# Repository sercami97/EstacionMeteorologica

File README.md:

# Estacion Meteorológica Inteligente de Bajo Costo

El objetivo del proyecto es diseñar una estación meteorológica inteligente. Esto es, que sea capaz de usar protocolos de IoT para el almacenamiento de los datos en un servidor remoto y ser autosostenible (Energía solar). Además, se espera que los diseños sean fácilmente replicables y tengan un bajo costo. Esto con el objetivo de ser más acesible para las comunidades campesinas y lograr un mayor impacto.

## Comenzando
Descarga o clona el repositorio a tu maquina local. En la capeta ../CodigoArduino/DATA_SERVIDOR_NSM encontrarán el codigo fuente del proyecto (Arduino). Por otro lado, en la carpeta ../PCB/LATEST/PCB_final se encuentran los archivos pertinentes al diseño de la PCB del proyecto. Dentro de esta misma carpeta, en ../GerberSleep se encuentran los archivos gerber listos para mandar a producción. Finalmente, en ../Diseños3D se encuentran los archivos de los diseños 3D desarrollados para la estructura de la estación. 

### Pre-requisitos
Es necesario tener instalados los siguientes sowftware para acceder a los archivos del proyecto:
- Arduino
- KiCad EDA
- Autodesk Inventor
- Libería de Arduino "DHT.h" https://github.com/adafruit/DHT-sensor-library/archive/master.zip
- Libería de Arduino "Arduino.h"
- Libería de Arduino "Wire.h"
- Libería de "ArduinoSoftwareSerial.h"
- Libería de Arduino "DS3232RTC.h" https://github.com/JChristensen/DS3232RTC

### Instalación
Para contar con un prototipo del proyecto debes:
- Imprimir, soldar y armar PCB (En la wiki se describe con mejor detalle como hacer esto junto con los componentes necesarios).
- Imprimir y replicar piezas 3D (En la wiki se describe con mejor detalle como hacer esto junto con los materiales necesarios).
- Armar estación (En la wiki se describe con mejor detalle como hacer esto junto con las piezas necesarias).

### Ejecutando pruebas

#### 1. Codigo Arduino
Para probar la funcionalidad del codigo de arduino, ubíquese en la carpeta ../CodigoArduino/DATA_SERVIDOR_NSM y ejecute el archivo DATA_SERVIDOR_NSM.ino con Arduino. Compila el programa en 'programa' -> 'Verificar/Compilar'. Verificar que no aparezca ningun error en la consola de salida.

#### 2. PCB
Para probar la funcionalidad de la PCB es necesario hacer pruebas de continuidad entre los nodos de la misma. Para esto, puedes usar un multimetro. Si todo está correcto, se puede pasar conectar los componentes y  alimentar la estación con su respectiva batería de litio. 

#### 4. Arduino + PCB
Una vez alimentada la PCB, puede conectar el arduino pro-mini a su ordenador haciendo uso de un cable y módulo FTDI. Ejecute el programa en Arduino y verifique que la placa en 'Herramientas' -> 'Placa' sea Arduino pro mini. Luego, suba el programa en 'Programa' -> 'Subir' y abra el serial en 'Herramientas' -> 'Monitor Serie'. Deberian comenzar a aparecer mensajes que indican la correcta ejecución del código.

#### 5. Funcionalidad
Configure los intervalos de medición de la estación y verifique la funcionalidad de los mensajes en el servidor: http://datos-env.iafjn3xg9q.us-east-1.elasticbeanstalk.com/datos/new/innovandes

#### 6. Estación Completa
Una vez verificados los pasos anteriores, se puede proceder a armar la estación completa con los diseños 3D. Armela y haga nuevamente la prueba del punto 5.

### Construido con
- Arduino
- KiCad EDA
- Autodesk Inventor

### Wiki 
Visita nuestra Wiki https://github.com/sercami97/EstacionMeteorologica/wiki para obtener mas información sobre el dearrollo y cómo utilizar este proyecto.

### Autores
- Iguarán Jorge - Diseños electrónicos y PCB 
- Rodriguez David - Código Arduino y Diseños electrónicos
- Sanabria Sergio - Diseños 3D y replicabilidad

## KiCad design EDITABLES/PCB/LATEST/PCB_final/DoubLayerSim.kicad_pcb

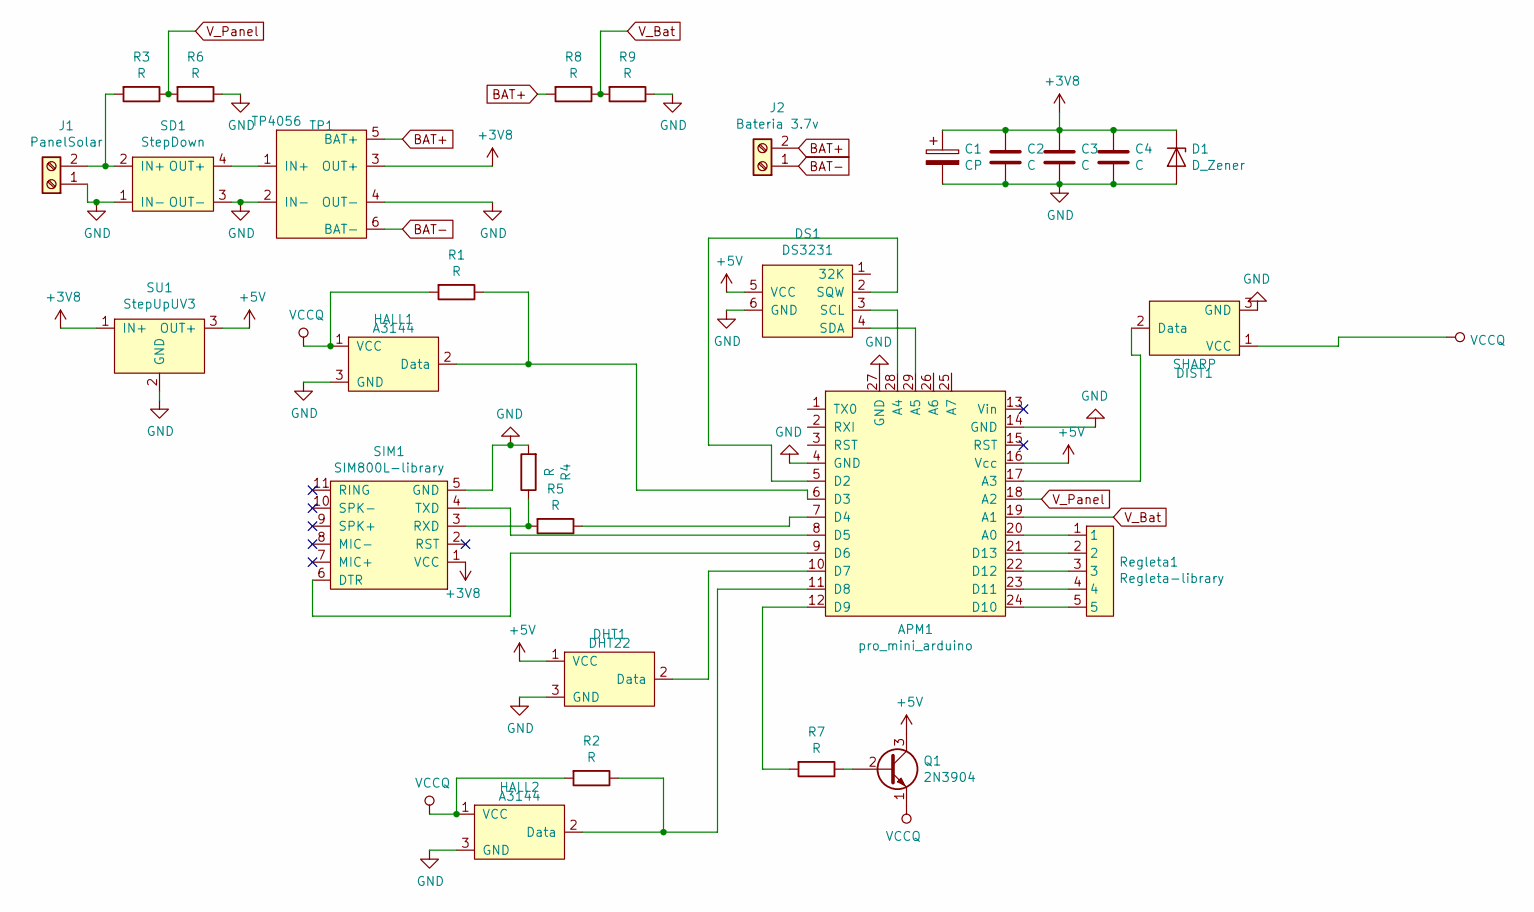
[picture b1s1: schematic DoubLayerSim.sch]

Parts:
APM1: pro_mini_arduino; mini_pro
C1: CP; CP_Radial_D10.0mm_P5.00mm
C2, C3, C4: C; C_Disc_D4.3mm_W1.9mm_P5.00mm
D1: D_Zener; D_T-1_P5.08mm_Horizontal
DHT1: DHT22
DIST1: SHARP; Hall
DS1: DS3231
HALL1, HALL2: A3144; Hall
J1: PanelSolar; TerminalBlock_bornier-2_P5.08mm
J2: Bateria 3.7v; TerminalBlock_bornier-2_P5.08mm
Q1: 2N3904; TO-92_Inline
R1, R2, R3, R4, R5, R6, R7, R8, R9: R; ResistorPCB
Regleta1: Regleta-library; PinHeader_1x05_P2.54mm_Vertical
SD1: StepDown; MP1584
SIM1: SIM800L-library; SIM800L
SU1: StepUpUV3; SU_U3V
TP1: TP4056; TP4056Pro

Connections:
+3V8: C1.1, C2.1, C3.1, C4.1, D1.1 (K), SIM1.1 (VCC), SU1.1 (IN+), TP1.3 (OUT+)
+5V: APM1.16 (Vcc), DHT1.1 (VCC), DS1.5 (VCC), Q1.3 (C), SU1.3 (OUT+)
BAT+: J2.2, R8.2, TP1.5 (BAT+)
BAT-: J2.1, TP1.6 (BAT-)
GND: APM1.4 (GND), APM1.14 (GND), APM1.27 (GND), C1.2, C2.2, C3.2, C4.2, D1.2 (A), DHT1.3 (GND), DIST1.3 (GND), DS1.6 (GND), HALL1.3 (GND), HALL2.3 (GND), J1.1, R4.2, R6.1, R9.1, SD1.1 (IN-), SD1.3 (OUT-), SIM1.5 (GND), SU1.2 (GND), TP1.2 (IN-), TP1.4 (OUT-)
unnamed: APM1.5 (D2), DS1.2 (SQW)
unnamed: APM1.6 (D3), HALL1.2 (Data), R1.1
unnamed: APM1.7 (D4), R5.1
unnamed: APM1.8 (D5), SIM1.4 (TXD)
unnamed: APM1.9 (D6), SIM1.6 (DTR)
unnamed: APM1.10 (D7), DHT1.2 (Data)
unnamed: APM1.11 (D8), HALL2.2 (Data), R2.1
unnamed: APM1.12 (D9), R7.2
unnamed: APM1.17 (A3), DIST1.2 (Data)
unnamed: APM1.20 (A0), Regleta1.1
unnamed: APM1.21 (D13), Regleta1.2
unnamed: APM1.22 (D12), Regleta1.3
unnamed: APM1.23 (D11), Regleta1.4
unnamed: APM1.24 (D10), Regleta1.5
unnamed: APM1.28 (A4), DS1.3 (SCL)
unnamed: APM1.29 (A5), DS1.4 (SDA)
unnamed: J1.2, R3.2, SD1.2 (IN+)
unnamed: Q1.2 (B), R7.1
unnamed: R4.1, R5.2, SIM1.3 (RXD)
unnamed: SD1.4 (OUT+), TP1.1 (IN+)
VCCQ: DIST1.1 (VCC), HALL1.1 (VCC), HALL2.1 (VCC), Q1.1 (E), R1.2, R2.2
V_Bat: APM1.19 (A1), R8.1, R9.2
V_Panel: APM1.18 (A2), R3.1, R6.2

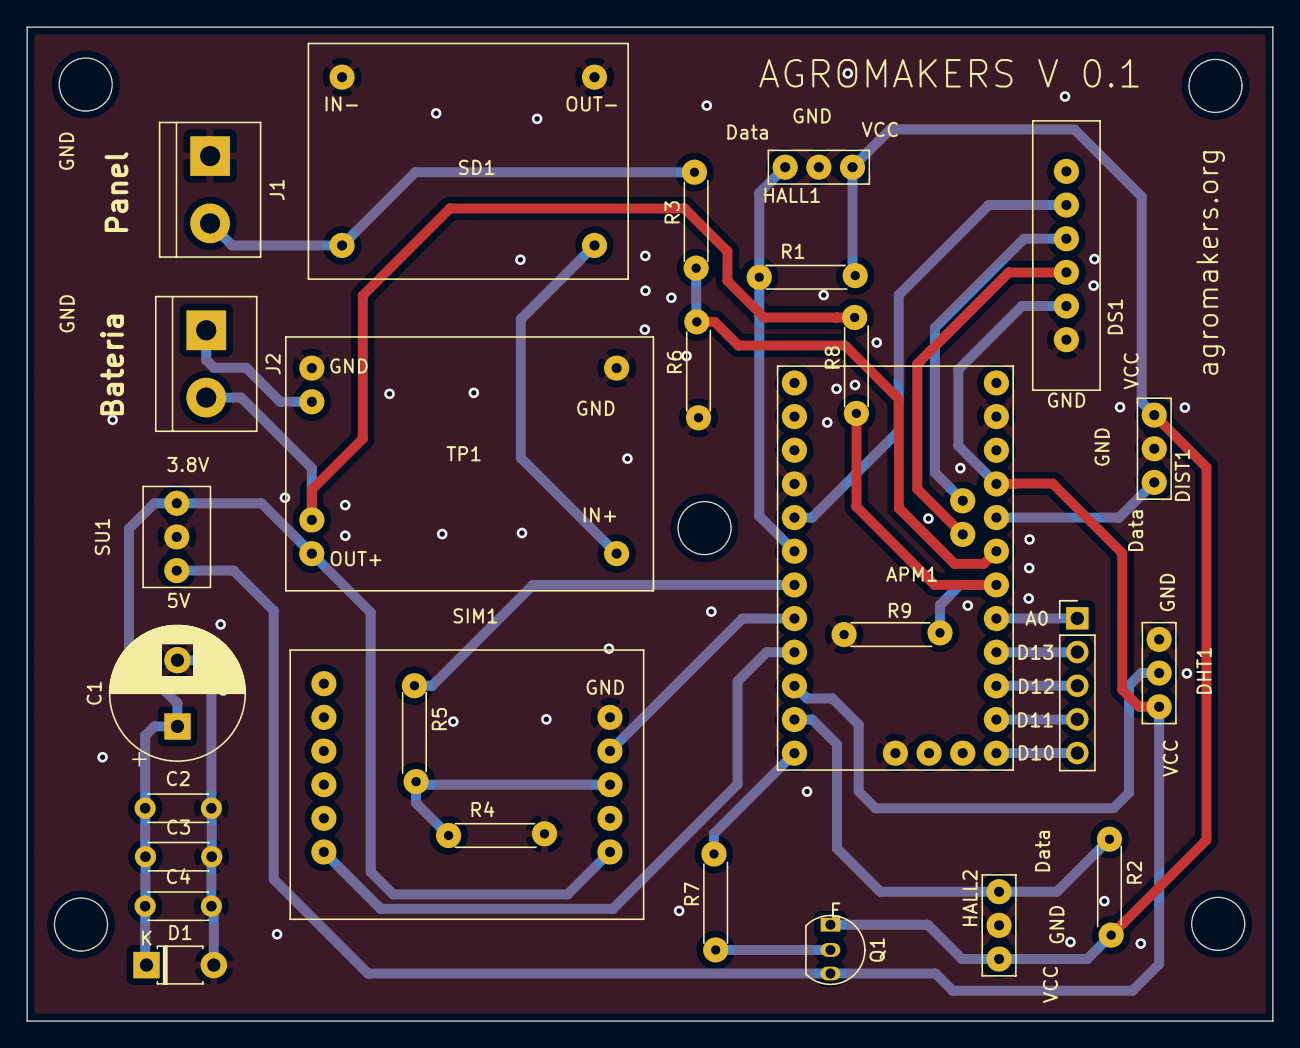
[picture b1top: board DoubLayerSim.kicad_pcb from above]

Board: 2 copper layers, 94.0 x 75.0 mm, 28 parts (0 on the bottom side), 28 nets.

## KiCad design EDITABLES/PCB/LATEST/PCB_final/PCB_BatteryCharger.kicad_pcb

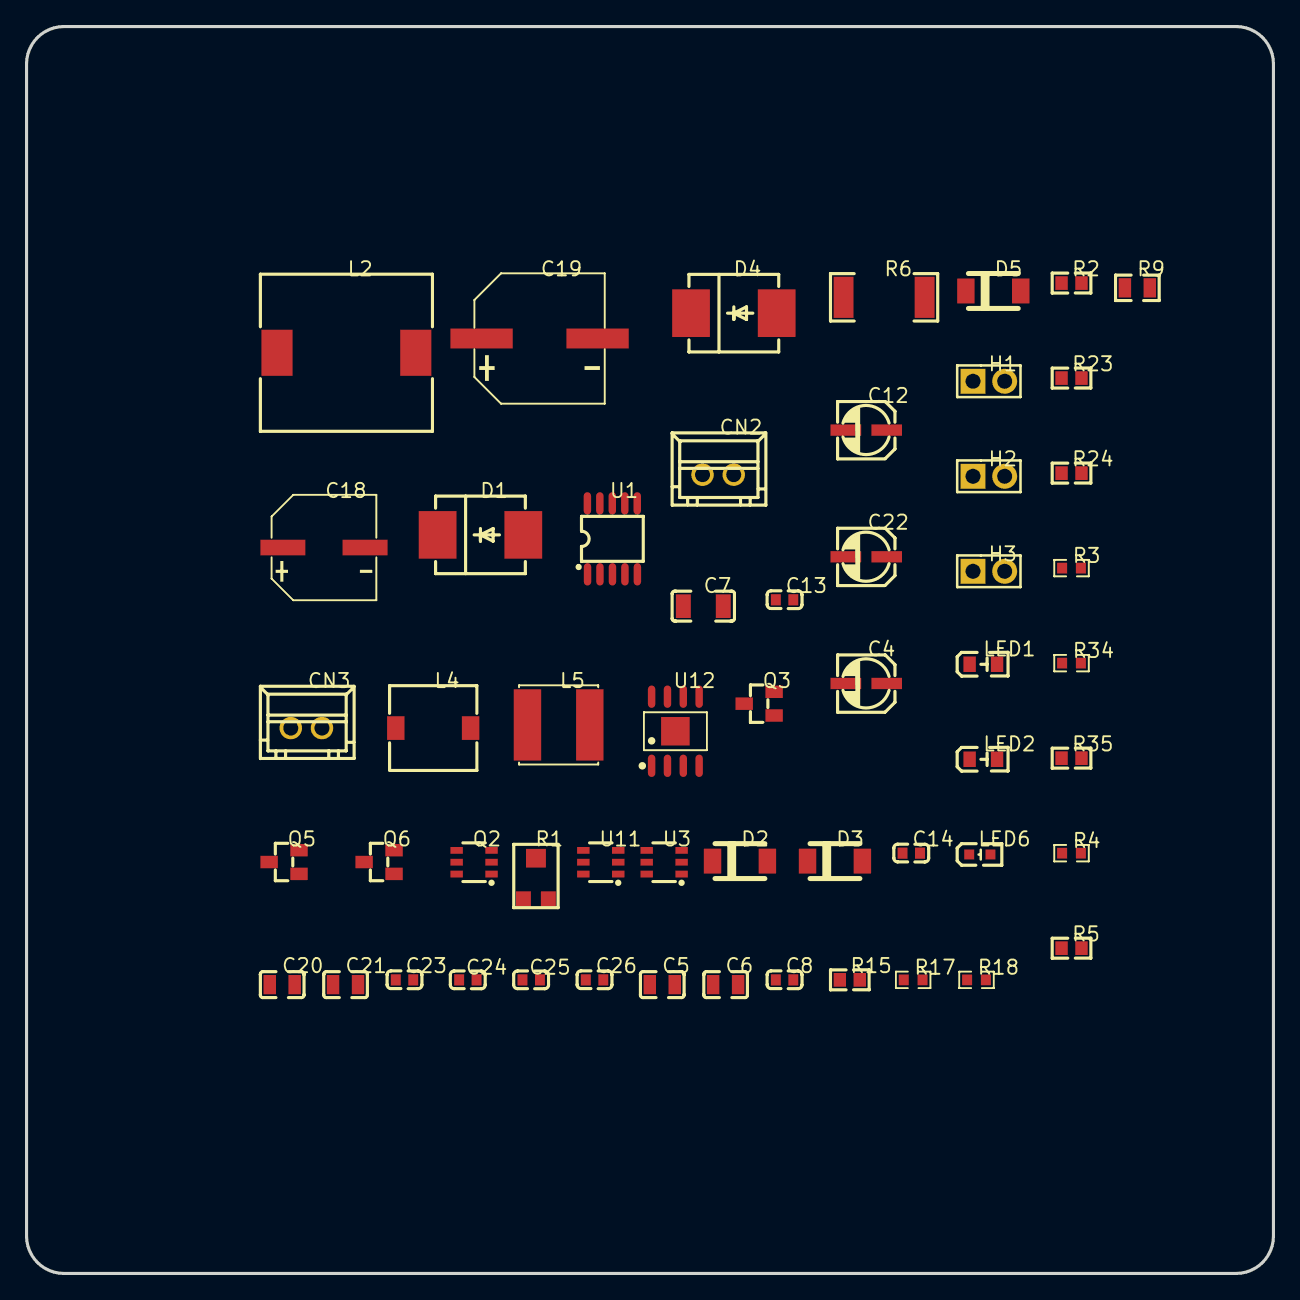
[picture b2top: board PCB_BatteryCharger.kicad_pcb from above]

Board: 2 copper layers, 100.0 x 100.0 mm, 55 parts (0 on the bottom side), 38 nets, no tracks yet.

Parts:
C4, C12, C22: 10uF; CAP-SMD_BD4.0-L4.3-W4.3-RD
C5, C6, C20, C21: 4.7uF; C0805
C7: 220nF; C1206
C8, C13, C23, C26: 100nF; C0603
C14: 470nF; C0603
C18: 470uF; CAP-SMD_BD8.0-L8.3-W8.3-FD
C19: 330uF; CAP-SMD_BD10.0-L10.3-W10.3-FD
C24: 33nF; C0603
C25: 10nF; C0603
CN2, CN3: XH-2A; CONN-TH_XH-2A
D1, D4: SS34; SMC_L7.1-W6.2-LS8.1-RD
D2: 0; SOD-128_L3.7-W2.5-LS4.7-RD
D3, D5: PMEG3020EP,115; SOD-128_L3.7-W2.5-LS4.7-RD
H1, H2, H3: CURR; HDR-TH_2P-P2.54-V-F
L2: 82uH; IND-SMD_L13.8-W12.6_SMMS1360
L4: 22uH; IND-SMD_L7.0-W6.8
L5: 47uH; IND-SMD_L6.0-W6.0
LED1: RED; LED0805-RD
LED2: YELLOW; LED0805-RD
LED6: BLUE; LED0603-R-RD
Q2: FS8205; SOT-23-6_L2.9-W1.6-P0.95-LS2.8-BR
Q3, Q5, Q6: AO3401A; SOT-23_L2.9-W1.3-P1.90-LS2.4-BR
R1: 15K; RES-ADJ-SMD_VG039NCHXTB153
R2, R35: 2K; R0603
R3: 100K; R0603
R4: 5.6K; R0603
R5, R15, R23: 1K; R0603
R6: 0.05; R2512
R9: 120; R0805
R17: 76.8K; R0603
R18: 16K; R0603
R24: 7.5K; R0603
R34: 100; R0603
U1: CN3791; SSOP-10_L4.9-W3.9-P1.00-LS6.0-BL
U3: FS312F-G; SOT-23-6_L2.9-W1.6-P0.95-LS2.8-BR
U11: MT3608; SOT-23-6_L2.9-W1.6-P0.95-LS2.8-BR
U12: TD1519AMR; SOP-8_L4.9-W3.9-P1.27-LS6.0-BL-EP

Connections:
+5V: C21.2, C22.1, D3.1, Q6.3, R24.2
BAT: C20.2, L4.1, U11.4, U11.5
BAT+: C4.1, C6.2, H2.1, R6.2, R34.2, U1.7
BAT-: C13.2, CN3.2, Q2.3, U3.6
BS: C25.1, U12.1
C24_1: C24.1, R4.2
CN2_1: CN2.1, D2.2
COMP: C24.2, U12.6
D1_2: D1.2, D4.2, L2.1
D4_1: D4.1, Q5.3
EN: R3.2, U12.7
GND: C4.2, C5.1, C6.1, C7.1, C12.2, C14.1, C18.2, C19.2, C20.1, C21.1, C22.2, C23.1, C26.1, CN2.2, D1.1, LED6.2, Q2.1, R2.1, R4.1, R15.2, R18.1, R23.1, U1.2, U11.2, U12.4, U12.9
H1_2: D2.1, H1.2
H2_2: CN3.1, H2.2
L4_2: D3.2, L4.2, U11.1
LED6_1: LED6.1, R35.1
MPPT: R1.3, R15.1, U1.6
Q6_2: Q3.2, Q6.2
R5_1: LED1.2, LED2.2, R5.1
R9_1: C7.2, R9.1
R23_2: R23.2, R24.1, U11.3
SS: C23.2, U12.8
SW: C25.2, L5.1, U12.3
U1_1: C8.2, U1.1
U1_3: LED1.1, U1.3
U1_4: LED2.1, U1.4
U1_5: R9.2, U1.5
U1_8: L2.2, R6.1, U1.8
U1_10: Q5.1, U1.10
U3_1: Q2.4, U3.1
U3_2: R2.2, U3.2
U3_3: Q2.6, U3.3
U3_5: C13.1, R34.1, U3.5
U12_5: R17.1, R18.2, U12.5
VOUT: D5.1, Q3.3
V_SOL: C5.2, C8.1, C12.1, C14.2, H1.1, Q5.2, R1.1, R5.2
V_SOLAR: C19.1, C26.2, Q3.1, Q6.1, R3.1, U12.2
V_SOL_5V: C18.1, D5.2, L5.2, R17.2

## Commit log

2020-03-27 basic
2020-03-27 Disenos3D
2020-04-06 Cambio PCB Devolucion China
2020-04-16 Se agrego ultima version PCB
2020-04-17 Se añadio codigo comentado
2020-04-17 PruebaVariosGit
2020-04-22 Programa que incluye toma de datos, subida al servidor y sleep mode del SIM800L
2020-04-23 Readme detallado
2020-04-23 Organización de carpetas de PCB
2020-04-25 Subiendo imagenes
2020-04-25 Mas imagenes
2020-04-25 Cambiando imagen de arduino
2020-04-25 imagen arduino
2020-04-25 Imagenes de diagramas
2020-04-25 Imagenes PCBs
2020-04-28 Adelanto diseños
2020-04-28 Se movio carpeta img a documentacion
2020-05-04 Programa que incluye toma de datos, subida al servidor, sleep mode por medio del modulo RTC y sleep mode del SIM800L
2020-06-29 Cambio 3D
2020-06-29 Se movieron editables a PROYECTO_GIT
2020-08-21 Programa que incluye toma de datos, envío al servidor, sleep mode por medio del modulo RTC y sleep mode del SIM800L
2020-10-17 Crear Datalogger_Final.ino
    Se creó el archivo con el programa final, en el que satisfactoriamente se sensan y se suben al servidor las variables de interés, haciendo uso del sleep mode.
2021-01-20 Backup code
2021-02-21 Update codigo limipio, basic ino test sim800l
2021-02-24 Prueba Sensores, Basic SIM800L and CodigoFinalProbado
2021-03-02 CodigoFinal envios estables
2021-03-06 CodigoFinal Protocolos,Sleep Mode, Minimum power mode
2021-03-16 Codigo Probado Campo
2021-03-20 PruebaSensores y SIM
2021-03-27 Codigo EfectoHall y Dir mejorado
2021-04-28 Actualizacion Codigo Arduino
2021-06-15 Update 15 JUN
2021-12-21 Dic 2021
